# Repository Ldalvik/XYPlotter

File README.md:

# XYPlotter
Homemade X/Y Plotter using StippleGen to create SVG files

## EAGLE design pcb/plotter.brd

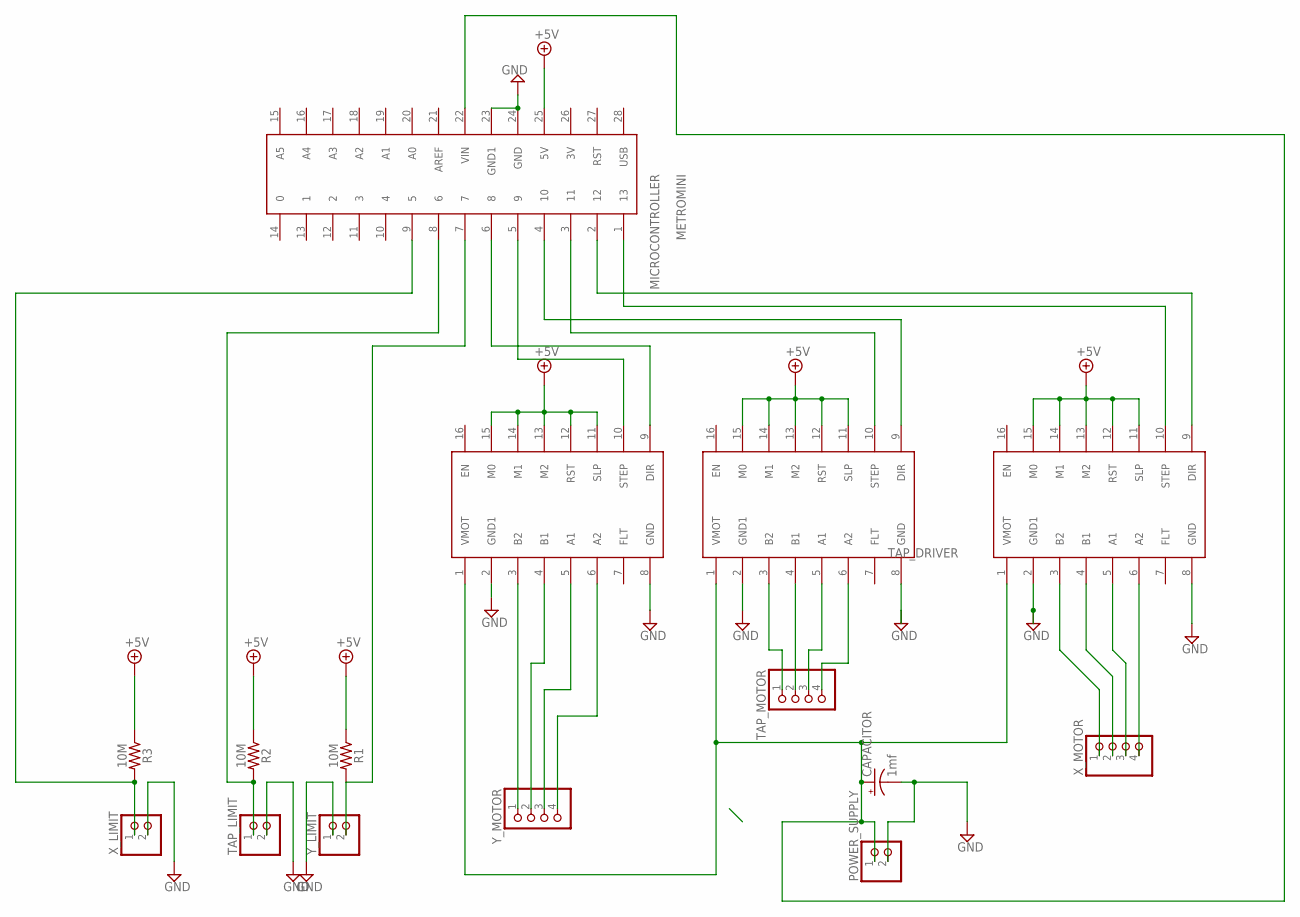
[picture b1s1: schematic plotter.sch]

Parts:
CAPACITOR: 1mf; CPOL-RADIAL-5MM-10MM-KIT
MICROCONTROLLER: METROMINI
POWER_SUPPLY: PINHD-1X2; 1X02
R1, R2, R3: 10M; AXIAL-0.3
TAP_DRIVER: DRV8825
TAP_LIMIT: PINHD-1X2; 1X02
TAP_MOTOR: PINHD-1X4; 1X04
X_DRIVER: DRV8825
X_LIMIT: PINHD-1X2; 1X02
X_MOTOR: PINHD-1X4; 1X04
Y_DRIVER: DRV8825
Y_LIMIT: PINHD-1X2; 1X02
Y_MOTOR: PINHD-1X4; 1X04

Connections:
12V: CAPACITOR.+, MICROCONTROLLER.22 (VIN), POWER_SUPPLY.1, TAP_DRIVER.1 (VMOT), X_DRIVER.1 (VMOT), Y_DRIVER.1 (VMOT)
+5V: MICROCONTROLLER.25 (5V), R1.P$1 (1), R2.P$1 (1), R3.P$1 (1), TAP_DRIVER.11 (SLP), TAP_DRIVER.12 (RST), TAP_DRIVER.13 (M2), TAP_DRIVER.14 (M1), TAP_DRIVER.15 (M0), X_DRIVER.11 (SLP), X_DRIVER.12 (RST), X_DRIVER.13 (M2), X_DRIVER.14 (M1), X_DRIVER.15 (M0), Y_DRIVER.11 (SLP), Y_DRIVER.12 (RST), Y_DRIVER.13 (M2), Y_DRIVER.14 (M1), Y_DRIVER.15 (M0)
GND: CAPACITOR.-, MICROCONTROLLER.23 (GND1), MICROCONTROLLER.24 (GND), POWER_SUPPLY.2, TAP_DRIVER.2 (GND1), TAP_DRIVER.8 (GND), TAP_LIMIT.2, X_DRIVER.2 (GND1), X_DRIVER.8 (GND), X_LIMIT.2, Y_DRIVER.2 (GND1), Y_DRIVER.8 (GND), Y_LIMIT.1
unnamed: MICROCONTROLLER.7, R1.P$2 (2), Y_LIMIT.2
unnamed: MICROCONTROLLER.5 (9), Y_DRIVER.10 (STEP)
unnamed: MICROCONTROLLER.9 (5), R3.P$2 (2), X_LIMIT.1
unnamed: MICROCONTROLLER.6 (8), Y_DRIVER.9 (DIR)
unnamed: MICROCONTROLLER.3 (11), TAP_DRIVER.10 (STEP)
unnamed: MICROCONTROLLER.4 (10), TAP_DRIVER.9 (DIR)
unnamed: MICROCONTROLLER.1 (13), X_DRIVER.10 (STEP)
unnamed: MICROCONTROLLER.2 (12), X_DRIVER.9 (DIR)
unnamed: MICROCONTROLLER.8 (6), R2.P$2 (2), TAP_LIMIT.1
unnamed: TAP_DRIVER.3 (B2), TAP_MOTOR.1
unnamed: TAP_DRIVER.4 (B1), TAP_MOTOR.2
unnamed: TAP_DRIVER.6 (A2), TAP_MOTOR.4
unnamed: X_DRIVER.3 (B2), X_MOTOR.1
unnamed: X_DRIVER.4 (B1), X_MOTOR.2
unnamed: X_DRIVER.5 (A1), X_MOTOR.3
unnamed: X_DRIVER.6 (A2), X_MOTOR.4
unnamed: Y_DRIVER.4 (B1), Y_MOTOR.2
unnamed: TAP_DRIVER.5 (A1), TAP_MOTOR.3
unnamed: Y_DRIVER.3 (B2), Y_MOTOR.1
unnamed: Y_DRIVER.5 (A1), Y_MOTOR.3
unnamed: Y_DRIVER.6 (A2), Y_MOTOR.4

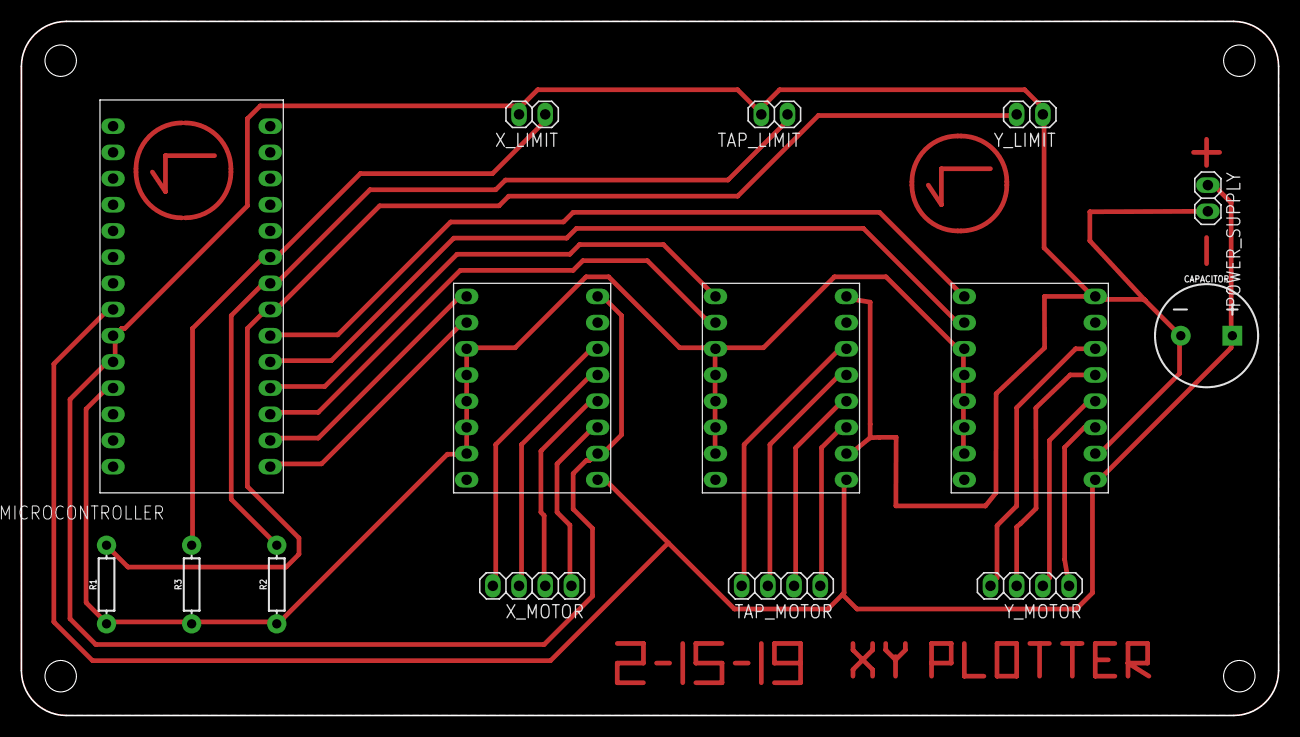
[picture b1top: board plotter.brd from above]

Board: 2 copper layers, 121.9 x 67.3 mm, 15 parts (0 on the bottom side), 24 nets.

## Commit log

2018-10-11 Create decimal(ignore)
2018-11-19 Rename main.java to Main.java
2019-02-12 Create j
2019-02-27 Rename plooter 2.sch to plotter.sch
2019-02-27 Rename plooter 2.brd to plotter.brd
2019-02-27 Create READ ME.md
    DEPRECATED, NOW USING RPI/SERIAL VIA WEBSERVER
2019-02-27 DEPRECATED, NOW USING RPI/SERIAL VIA WEBSERVER
2019-02-27 Control interface served by webserver
2019-03-08 Raspberry Pi support
2019-09-04 added reflective sensor for image marking/paper scroll
2020-01-16 Updated and commented code

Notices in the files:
parts and their libraries:
SparkFun-Resistors: Licensing: Creative Commons ShareAlike 4.0 International - https://creativecommons.org/licenses/by-sa/4.0
